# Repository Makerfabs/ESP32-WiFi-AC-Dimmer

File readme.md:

# Makerfabs ESP32 WiFi AC Dimmer

```c++
/*
Version:        V1.0
Author:            Vincent
Create Date:    2023/8/7
Note:

*/
```

[TOC]

# Makerfabs

[Makerfabs home page](https://www.makerfabs.com/)

[Makerfabs Wiki](https://wiki.makerfabs.com/)

# Makerfabs ESP32 WiFi AC Dimmer

## Intruduce

Product Link ：[WIFI AC Dimmer Switch](https://www.makerfabs.com/wifi-ac-dimmer-switch.html) 

Wiki Link : 

Arduino ATmega328P as MCU, inherited Ra-08 Lorawan module and 4 relays.

## Feature

- On-board AC-DC, No external power supply needed;
- On Board Relay to totally shut down current leakage;
- ESP32;
- Suitable for AC 110V~230V, Any frequency;
- Max Load: 2KW;

### Front:

### Back:

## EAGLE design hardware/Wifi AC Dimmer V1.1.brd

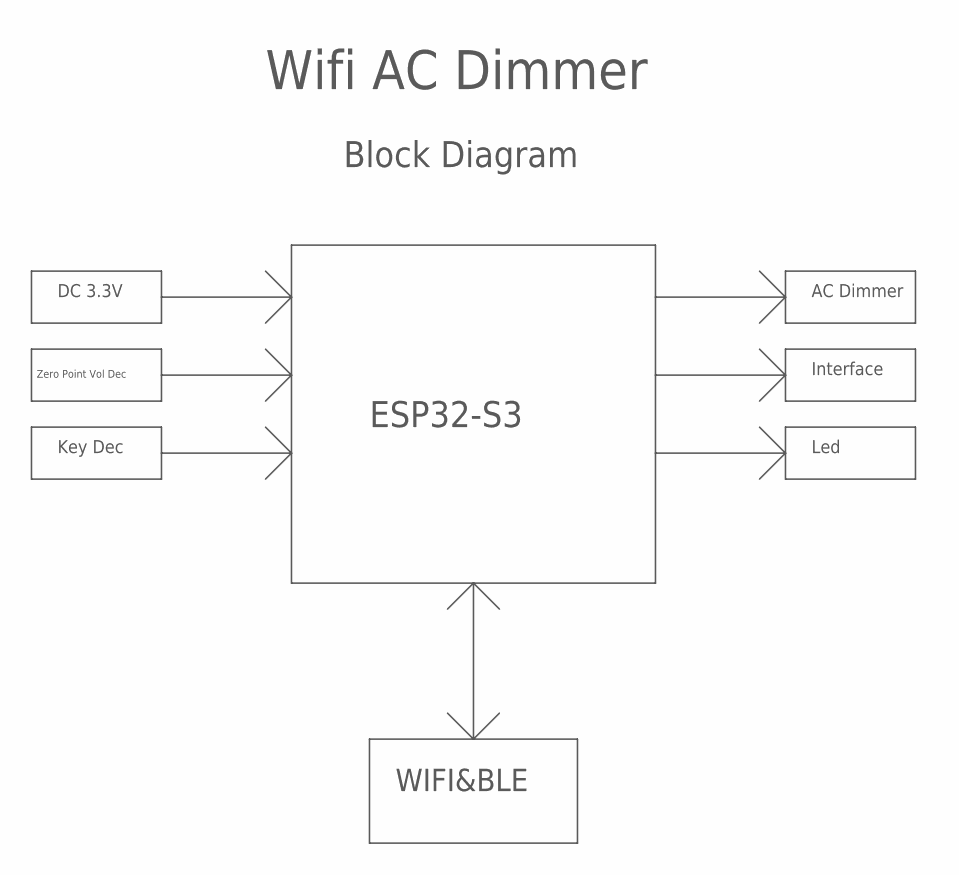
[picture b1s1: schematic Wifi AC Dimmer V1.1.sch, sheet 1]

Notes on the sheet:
ESP32-S3
DC 3.3V
Zero Point Vol Dec
Key Dec
AC Dimmer
Interface
Led
WIFI&BLE
Block Diagram
Wifi AC Dimmer

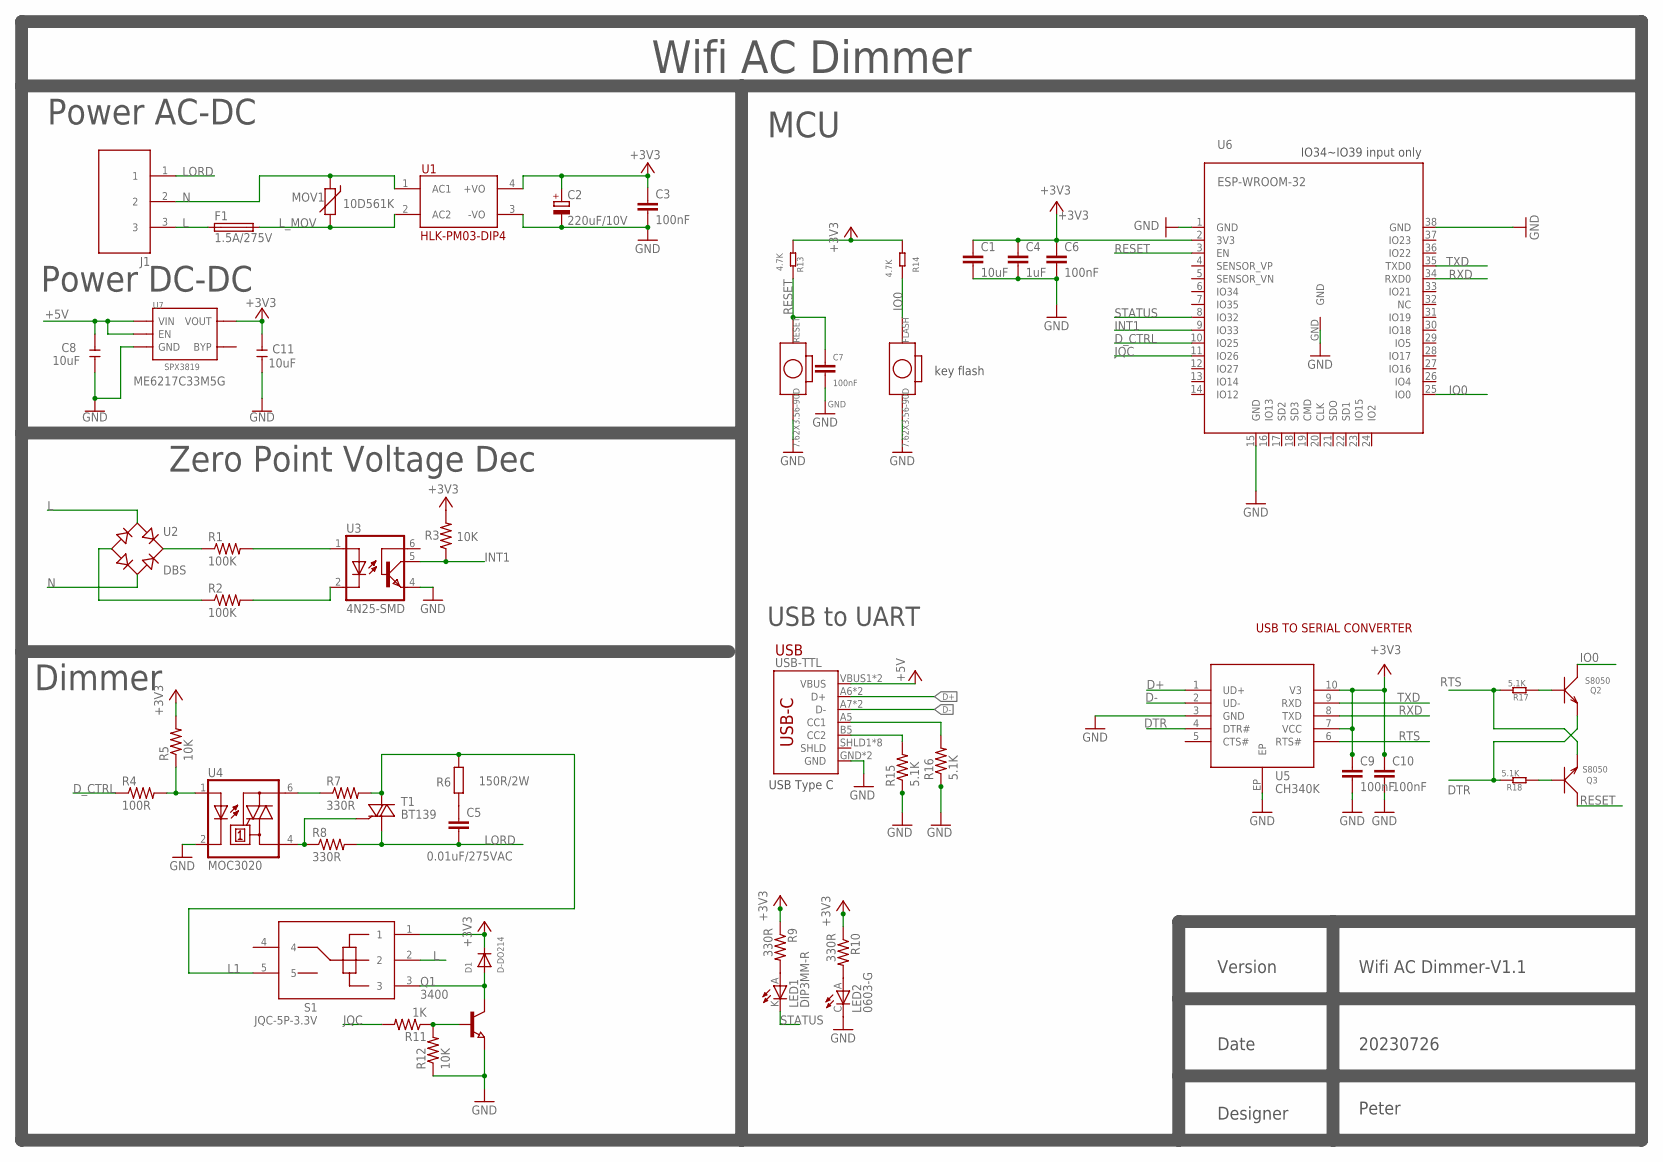
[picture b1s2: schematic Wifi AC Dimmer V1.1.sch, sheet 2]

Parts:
C1, C8, C11: 10uF; C0603
C2: 220uF/10V; SMD-6.3*5
C3, C6, C7, C9, C10: 100nF; C0603
C4: 1uF; C0603
C5: 0.01uF/275VAC; XC10B6
D1: D-DO214; DO-214
F1: 1.5A/275V; PICOFUSE
FLASH: 7.62X3.56-90D; 2P-7.62X3.56-90D
J1: DBT50G-9.5-3P; THROUGH-HOLE-9.5
LED1: DIP3MM-R; LED-3MM
LED2: 0603-G; LED0603
MOV1: 10D561K; S10K11
Q1: 3400; SOT-23
Q2, Q3: S8050; SOT23
R1, R2: 100K; R0805
R3, R5, R12: 10K; R0603
R4: 100R; R0603
R6: 150R/2W; R-0617
R7, R8: 330R; R0805
R9, R10: 330R; R0603
R11: 1K; R0603
R13, R14: 4.7K; R0603
R15, R16, R17, R18: 5.1K; R0603
RESET: 7.62X3.56-90D; 2P-7.62X3.56-90D
S1: JQC-5P-3.3V; JQC-5P-5V
T1: BT139; TO220CL
U1: HLK-PM03-DIP4; HLK-PM03
U2: DBS; DB-S
U3: 4N25-SMD; DIL6-SMD
U4: MOC3020; DIL6-SMD
U5: CH340K; ESOP-10-EP-150MIL
U6: ESP-WROOM-32
U7: SPX3819; SOT23-5
USB-TTL: USB_C5; USB-C-16P-5

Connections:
+3V3: C1.1, C2.+, C3.1, C4.1, C6.1, C9.1, C10.1, C11.2, D1.C, R3.2, R5.2, R9.1, R10.1, R13.2, R14.2, S1.1, U1.4 (+VO), U5.7 (VCC), U5.10 (V3), U6.2 (3V3), U7.5 (VOUT)
+5V: C8.2, U7.1 (VIN), U7.3 (EN), USB-TTL.VBUS1 (VBUS), USB-TTL.VBUS2 (VBUS)
D+: U5.1 (UD+), USB-TTL.A6 (D+), USB-TTL.B6 (D+)
D-: U5.2 (UD-), USB-TTL.A7 (D-), USB-TTL.B7 (D-)
DTR: Q2.2 (E), R18.1, U5.4 (DTR#)
D_CTRL: R4.1, U6.10 (IO25)
GND: C1.2, C2.-, C3.2, C4.2, C6.2, C7.2, C8.1, C9.2, C10.2, C11.1, FLASH.P$2 (2), LED2.C, Q1.2 (E), R12.1, R15.1, R16.1, RESET.P$2 (2), U1.3 (-VO), U3.4 (EMI), U4.2 (C), U5.3 (GND), U5.EP, U6.1 (GND), U6.15 (GND), U6.38 (GND), U6.GND, U7.2 (GND), USB-TTL.GND, USB-TTL.GND2 (GND)
INT1: R3.1, U3.5 (COL), U6.9 (IO33)
IO0: FLASH.P$1 (1), Q2.3 (C), R14.1, U6.25 (IO0)
JQC: R11.2, U6.11 (IO26)
L: F1.1, J1.3, S1.2, U2.AC1
L1: R6.2, R7.2, S1.5, T1.A (A2)
LORD: C5.2, J1.1, R8.2, T1.C (A1)
L_MOV: F1.2, MOV1.2, U1.2 (AC2)
N: J1.2, MOV1.1, U1.1 (AC1), U2.AC2
unnamed: Q1.1 (B), R11.1, R12.2
unnamed: D1.A, Q1.3 (C), S1.3
unnamed: R1.2, U3.1 (A)
unnamed: R2.1, U2.-
unnamed: R2.2, U3.2 (C)
unnamed: R7.1, U4.6 (A2)
unnamed: R8.1, T1.G, U4.4 (A1)
unnamed: C5.1, R6.1
unnamed: LED1.A, R9.2
unnamed: R4.2, R5.1, U4.1 (A)
unnamed: LED2.A, R10.2
unnamed: Q3.1 (B), R18.2
unnamed: Q2.1 (B), R17.2
unnamed: R1.1, U2.+
unnamed: R16.2, USB-TTL.A5 (CC1)
unnamed: R15.2, USB-TTL.B5 (CC2)
RESET: C7.1, Q3.3 (C), R13.1, RESET.P$1 (1), U6.3 (EN)
RTS: Q3.2 (E), R17.1, U5.6 (RTS#)
RXD: U5.8 (TXD), U6.34 (RXD0)
STATUS: LED1.K (C), U6.8 (IO32)
TXD: U5.9 (RXD), U6.35 (TXD0)

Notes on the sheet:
Wifi AC Dimmer
Power AC-DC
Zero Point Voltage Dec
Dimmer
MCU
Version
Date
Designer
Wifi AC Dimmer-V1.1
20230726
Peter
IO34~IO39 input only
key flash
USB to UART
USB TO SERIAL CONVERTER
USB
USB Type C
ME6217C33M5G
Power DC-DC

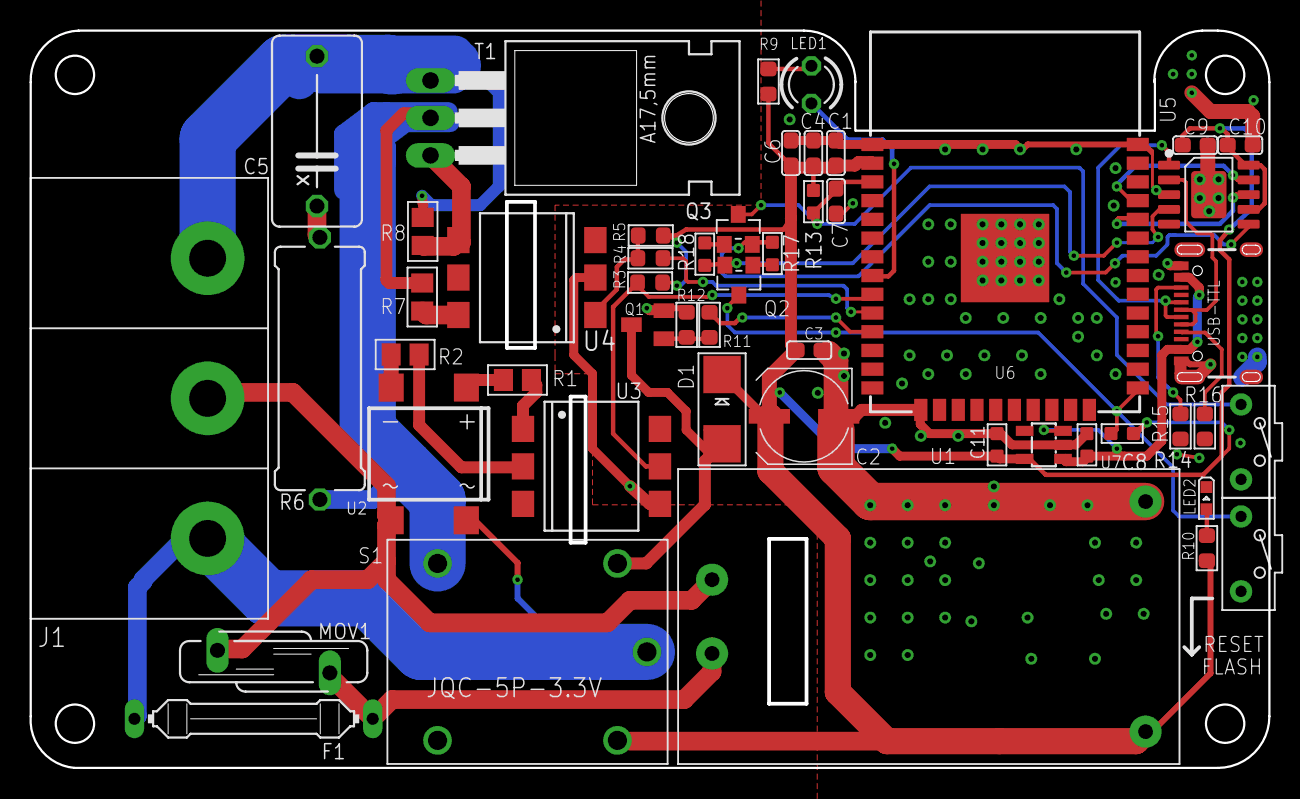
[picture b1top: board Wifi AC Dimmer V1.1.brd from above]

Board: 2 copper layers, 83.9 x 49.9 mm, 51 parts (1 on the bottom side), 36 nets.

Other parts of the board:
U$6: MAKERFABS_0.3

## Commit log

2023-08-05 Create
2024-06-08 Fix pin error

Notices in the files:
parts and their libraries:
SparkFun-Aesthetics: Licensing: Creative Commons ShareAlike 4.0 International - https://creativecommons.org/licenses/by-sa/4.0
